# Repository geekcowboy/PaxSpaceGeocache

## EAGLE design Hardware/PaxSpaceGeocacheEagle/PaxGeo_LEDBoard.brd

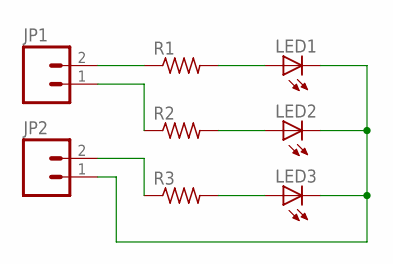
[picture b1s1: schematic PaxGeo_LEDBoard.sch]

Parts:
JP1, JP2: M023.5MM; SCREWTERMINAL-3.5MM-2
LED1, LED2, LED3: LED3MM
R1, R2, R3: R-US_0204/7; 0204/7

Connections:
GND: JP2.1, LED1.K (C), LED2.K (C), LED3.K (C)
unnamed: JP1.2, R1.1
unnamed: JP1.1, R2.1
unnamed: JP2.2, R3.1
unnamed: LED1.A, R1.2
unnamed: LED2.A, R2.2
unnamed: LED3.A, R3.2

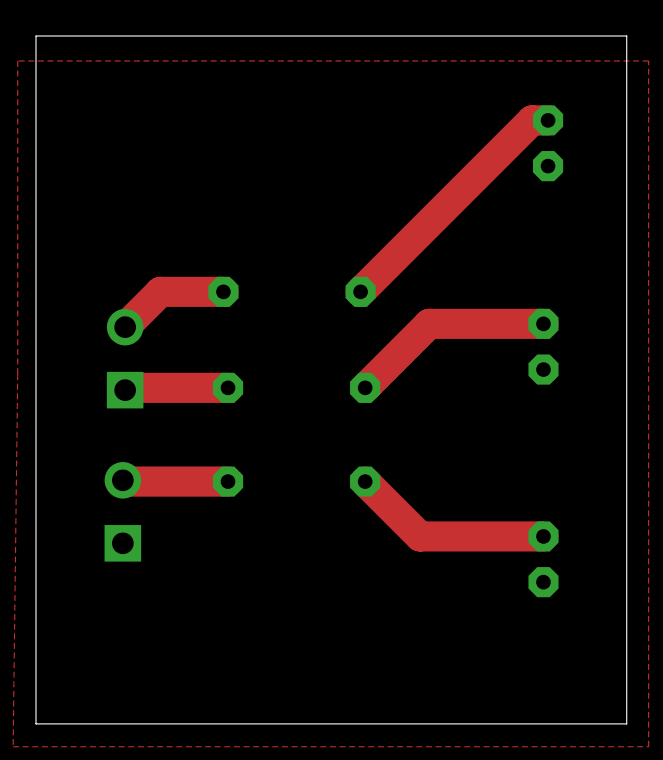
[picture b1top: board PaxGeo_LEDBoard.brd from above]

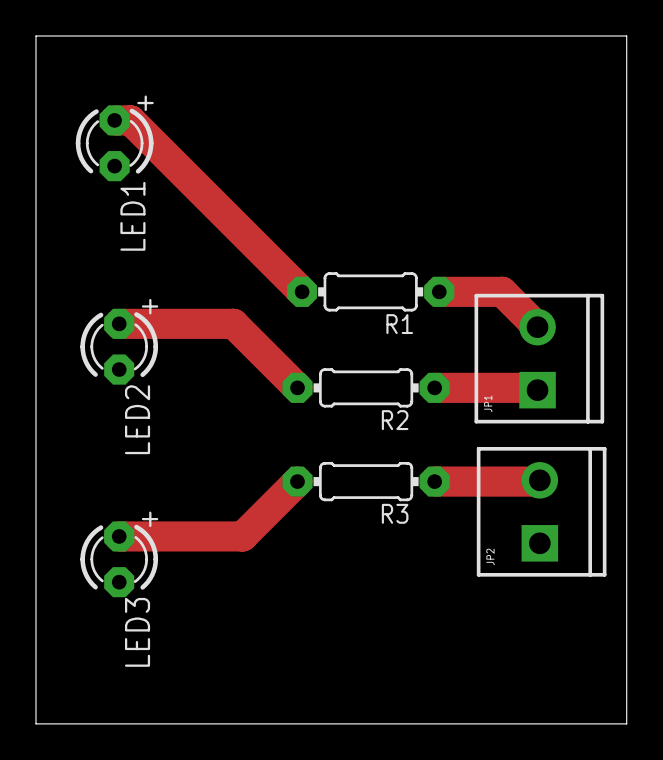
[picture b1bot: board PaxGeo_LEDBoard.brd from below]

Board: 2 copper layers, 32.8 x 38.2 mm, 8 parts (8 on the bottom side), 7 nets.

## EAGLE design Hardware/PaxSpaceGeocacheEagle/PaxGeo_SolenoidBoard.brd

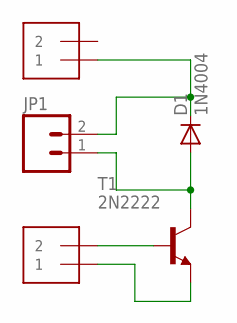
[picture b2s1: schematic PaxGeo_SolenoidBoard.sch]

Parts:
D1: 1N4004; DO41-10
J1, J2: 1X2-3.5MM
JP1: M02LOCK_LONGPADS; 1X02_LOCK_LONGPADS
T1: 2N2222; TO92-EBC-OVAL

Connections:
unnamed: J1.2, T1.B
unnamed: J1.1, T1.E
unnamed: D1.C, J2.1, JP1.2
unnamed: D1.A, JP1.1, T1.C

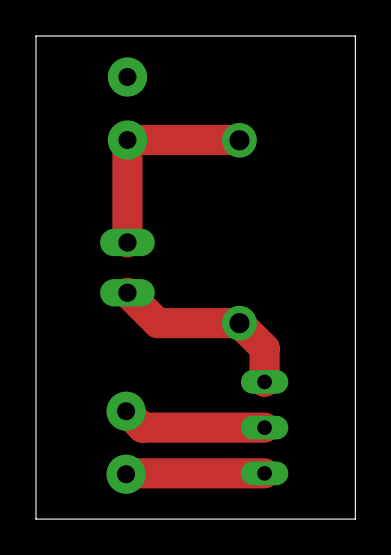
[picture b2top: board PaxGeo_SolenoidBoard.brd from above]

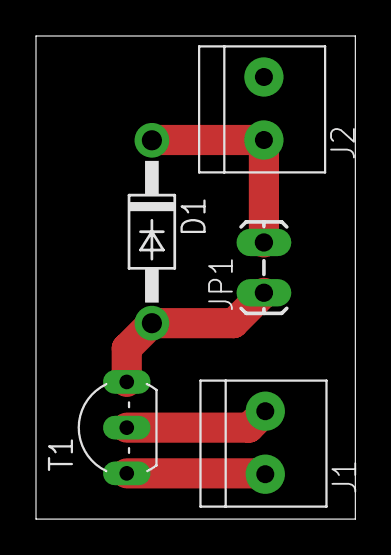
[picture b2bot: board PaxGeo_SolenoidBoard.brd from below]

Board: 2 copper layers, 17.7 x 26.8 mm, 5 parts (5 on the bottom side), 4 nets.

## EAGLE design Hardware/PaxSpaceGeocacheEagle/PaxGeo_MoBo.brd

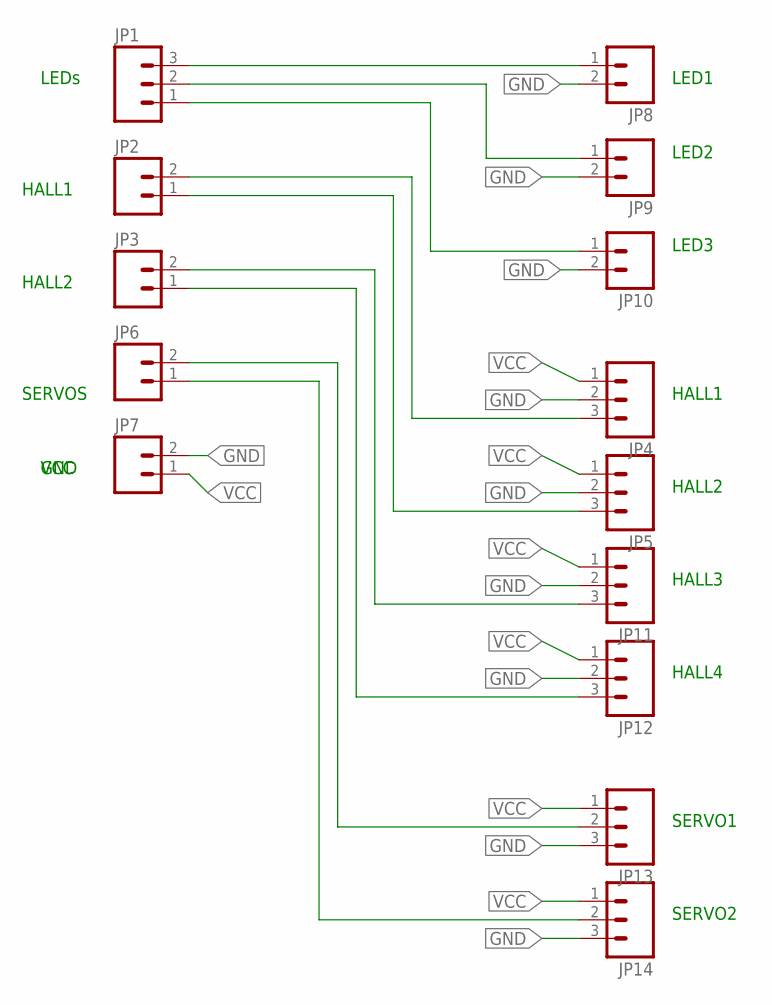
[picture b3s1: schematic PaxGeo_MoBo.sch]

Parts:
JP1, JP4, JP5, JP11, JP12, JP13, JP14: M03SCREW; SCREWTERMINAL-3.5MM-3
JP2, JP3, JP6, JP7, JP8, JP9, JP10: M023.5MM; SCREWTERMINAL-3.5MM-2

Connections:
GND: JP4.2, JP5.2, JP7.2, JP8.2, JP9.2, JP10.2, JP11.2, JP12.2, JP13.3, JP14.3
unnamed: JP1.3, JP8.1
unnamed: JP1.2, JP9.1
unnamed: JP1.1, JP10.1
unnamed: JP2.2, JP4.3
unnamed: JP2.1, JP5.3
unnamed: JP3.2, JP11.3
unnamed: JP3.1, JP12.3
unnamed: JP6.2, JP13.2
unnamed: JP6.1, JP14.2
VCC: JP4.1, JP5.1, JP7.1, JP11.1, JP12.1, JP13.1, JP14.1

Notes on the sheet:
VCC
GND
SERVOS
HALL2
HALL1
LEDs
LED1
LED2
LED3
HALL3
HALL4
SERVO1
SERVO2

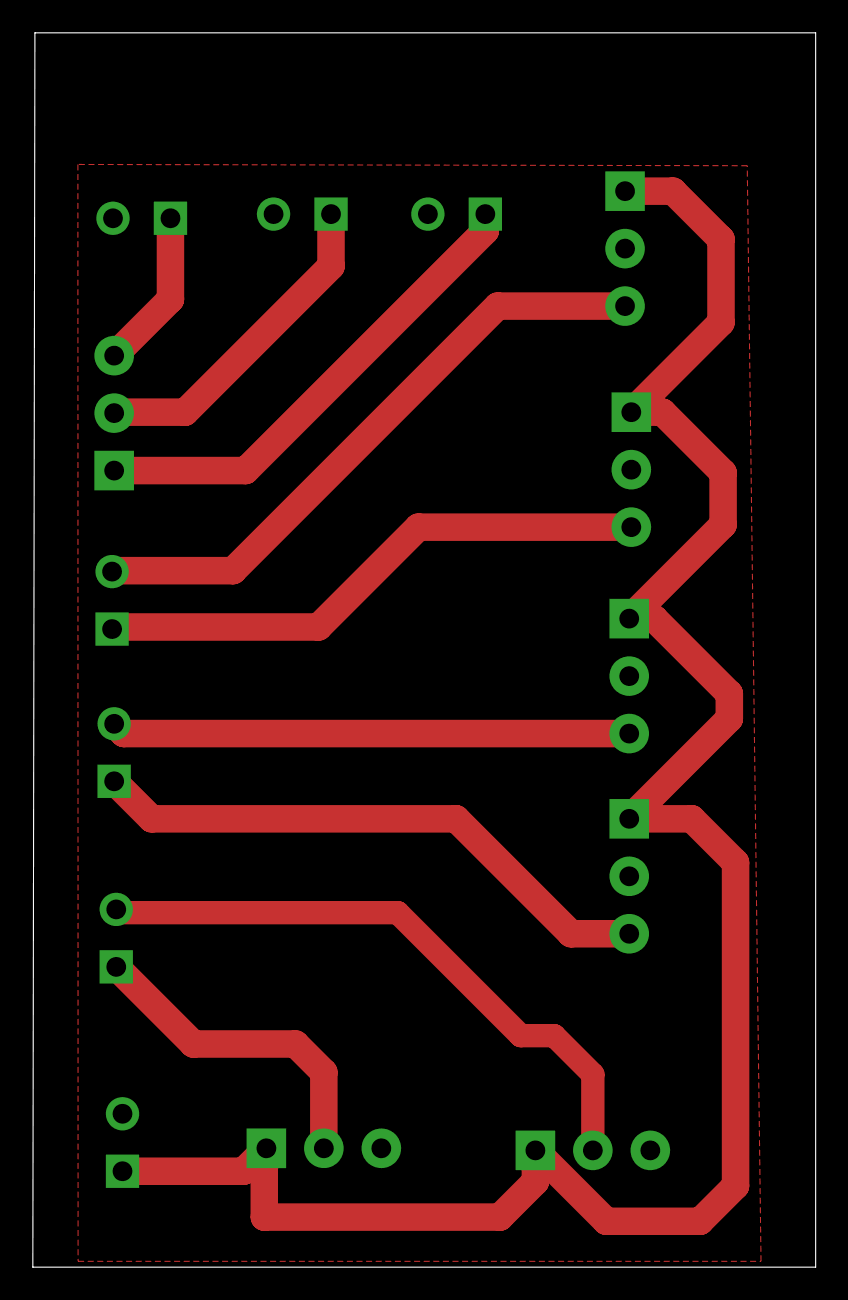
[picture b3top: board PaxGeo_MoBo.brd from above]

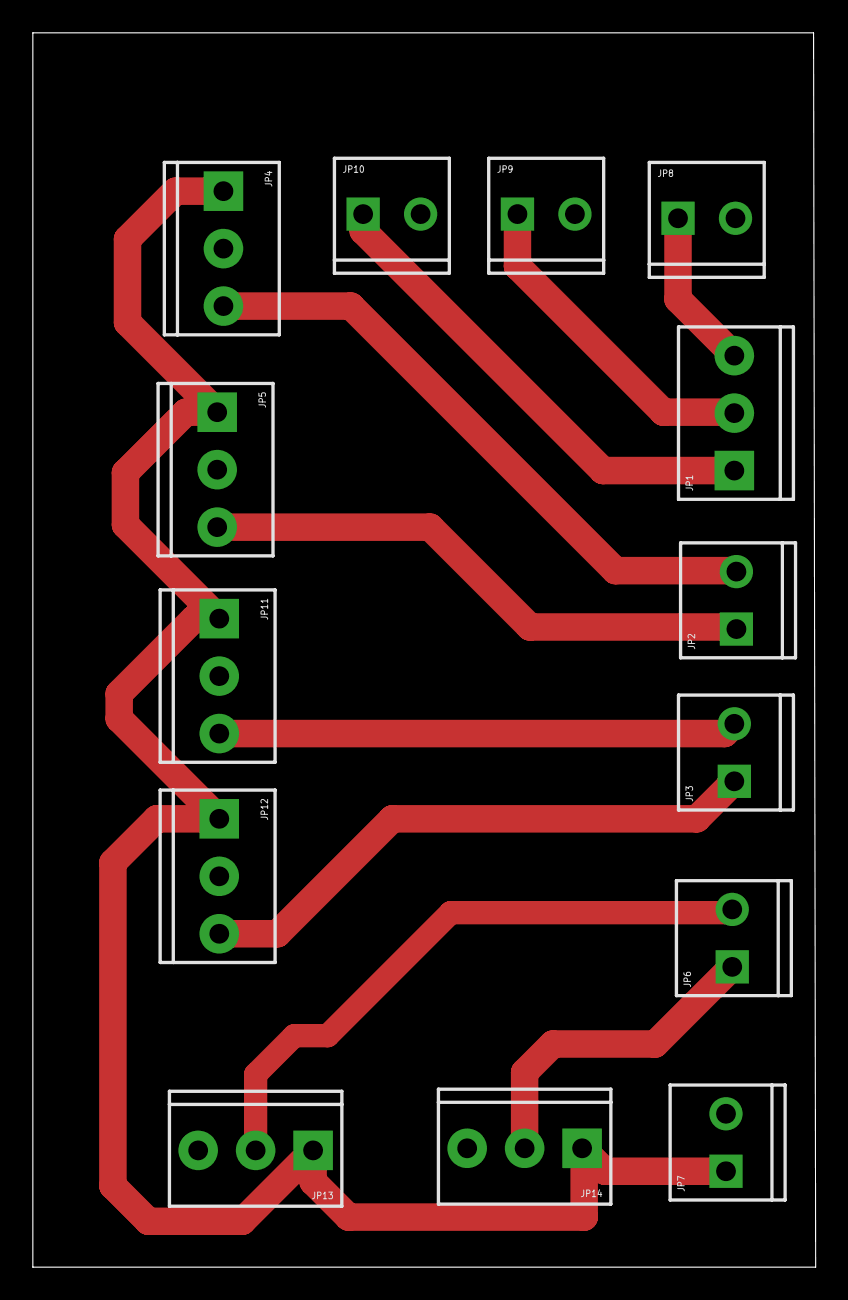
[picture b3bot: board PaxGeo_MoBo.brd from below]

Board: 2 copper layers, 47.7 x 75.2 mm, 14 parts (14 on the bottom side), 11 nets.

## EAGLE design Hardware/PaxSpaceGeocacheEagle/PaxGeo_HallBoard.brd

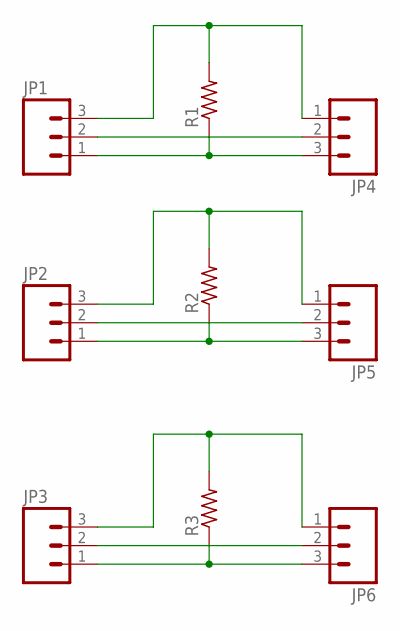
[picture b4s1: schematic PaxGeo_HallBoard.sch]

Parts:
JP1, JP2, JP3, JP4, JP5, JP6: M03SCREW; SCREWTERMINAL-3.5MM-3
R1, R2, R3: R-US_0204/7; 0204/7

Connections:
unnamed: JP1.3, JP4.1, R1.2
unnamed: JP1.1, JP4.3, R1.1
unnamed: JP1.2, JP4.2
unnamed: JP2.2, JP5.2
unnamed: JP2.3, JP5.1, R2.2
unnamed: JP2.1, JP5.3, R2.1
unnamed: JP3.2, JP6.2
unnamed: JP3.3, JP6.1, R3.2
unnamed: JP3.1, JP6.3, R3.1

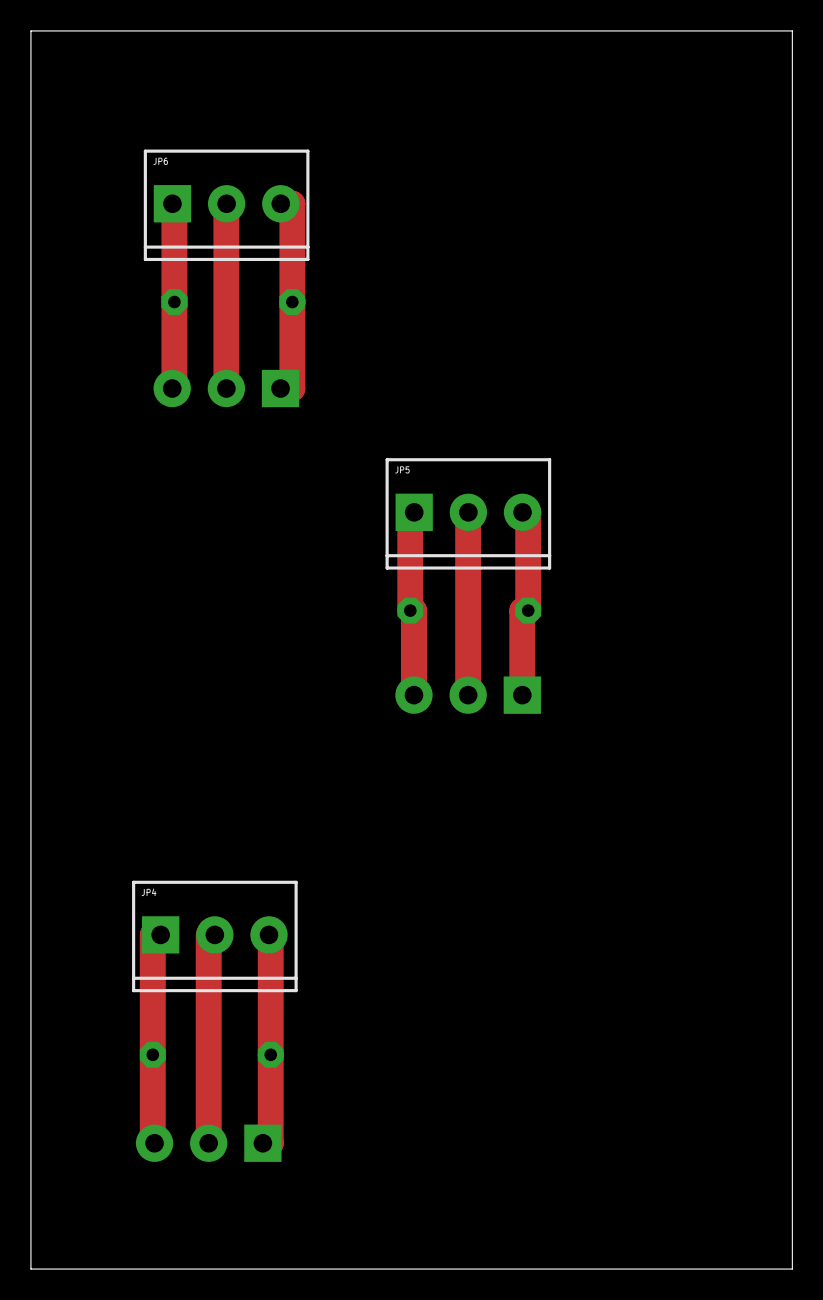
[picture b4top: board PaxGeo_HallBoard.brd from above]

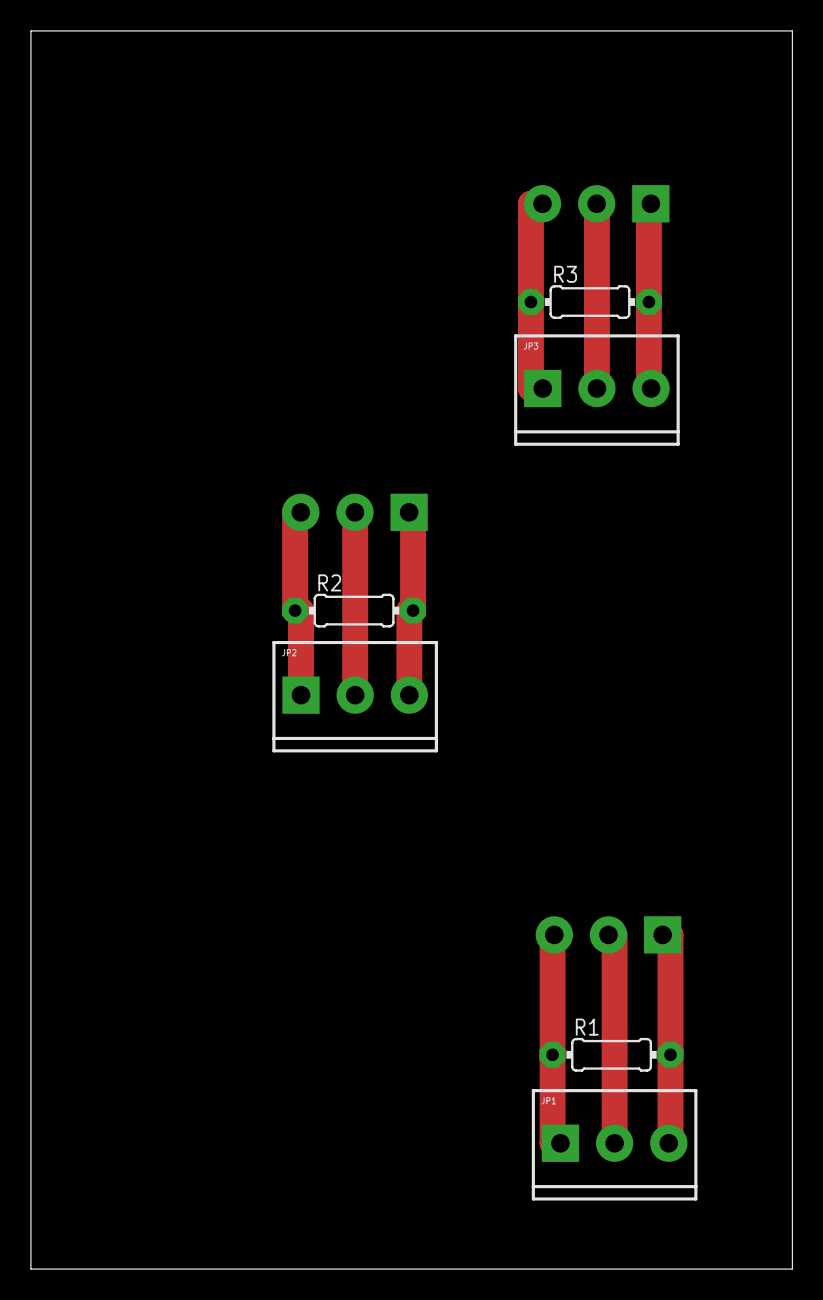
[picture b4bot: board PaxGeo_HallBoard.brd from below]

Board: 2 copper layers, 49.2 x 80.0 mm, 9 parts (6 on the bottom side), 9 nets.

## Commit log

2016-04-24 init commit
    firmware version 0.1
2016-04-25 init hardware design files commit
2016-04-25 switch from Solenoid to Servo
    Lock mechanism will now be accomplished with a servo
2016-04-27 Eagle files for LED board
2016-04-27 3D Printer files for magnet-holding pen
2016-04-28 renamed function flashLED10() to flashLED()
2016-04-29 servo corrections
    corrected the pulse variable to ensure proper open and lock positions
2016-04-30 Hall Sensor and Servo Holder 3D files created
2016-04-30 Servo code update
    Corrected code for open and locking servos, Servo1 is left servo,
    Servo2 is right servo

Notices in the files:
parts and their libraries:
SparkFun-Connectors: Licensing: Creative Commons ShareAlike 4.0 International - https://creativecommons.org/licenses/by-sa/4.0
